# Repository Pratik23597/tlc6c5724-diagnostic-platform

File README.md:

# Portable Automotive RGB Lighting Diagnostic Platform

**Development and Validation of a Portable Automotive RGB Lighting Diagnostic Platform Using the TLC6C5724-Q1 Automotive LED Driver with Local Control and MQTT-Based Remote Monitoring through Node-RED**

University project, OTH Regensburg (2026) - Pratik Sukare

An ESP32-based test and control unit for the Texas Instruments **TLC6C5724-Q1**, a 24-channel constant-current RGB LED driver for automotive lighting. The platform drives all 24 outputs, runs the driver's built-in diagnostics, and reports faults both on a local TFT display and on a remote Node-RED dashboard over MQTT.

## Features

- **Driver interface:** SPI-based serial control of the TLC6C5724-Q1 with separate LATCH, GCLK/BLANK PWM timing and the ERR fault line
- **Diagnostics:** LED open/short (LOD/LSD), short-to-ground, adjacent-pin short (APS), IREF open/short, thermal warning and over-temperature, LOD/LSD self-test, NEG/GCLK integrity test, device status, raw SID readout, error clear
- **Validated under controlled fault conditions:** open and shorted LEDs, short-to-ground, adjacent-pin shorts and IREF faults are detected as expected
- **Non-blocking firmware:** no long delays in the main loop; MQTT commands are queued as pending commands and executed by the main loop; automatic LED tests run as a state machine
- **Six automatic LED tests:** RGB colour cycle, RGB phase rotation, sequential chase, brightness sweep, all white, all off
- **Local HMI:** 128x160 SPI colour TFT and three push buttons - works without any network
- **Remote monitoring:** Eclipse Mosquitto + Node-RED Dashboard 2 with a diagnostics page and a per-channel LED control page (grayscale, dot correction)
- **Network recovery:** retries saved Wi-Fi profiles, and returns to the preferred hotspot if the MQTT broker is unreachable

| Prototype | Node-RED diagnostics |
|---|---|
|  |  |

## Reports

- [Project report](reports/Project_Report.pdf) - design, implementation and results
- [Diagnostic validation report](reports/Diagnostic_Validation_Report.pdf) - test method, fault-injection steps and recorded results for every diagnostic

## Repository layout

| Path | Contents |
|---|---|
| `firmware/TLC6C5724_Diagnostic_Controller/` | ESP32 Arduino sketch, split by module (see below) |
| `node-red/flows.json` | Node-RED Dashboard 2 flow (import via *Menu > Import*) |
| `hardware/` | KiCad schematics (plus a PDF export) of the prototype, and the TLC breakout schematic and PCB layout |
| `mosquitto/` | Mosquitto demo config and a Windows launcher that starts Mosquitto and Node-RED and opens the dashboard |
| `docs/images/` | Architecture, prototype and dashboard figures |
| `reports/` | Project report (paper) and diagnostic validation report with test procedures and results |

Firmware modules:

- `TLC6C5724_Diagnostic_Controller.ino` - declarations and setup / main loop
- `TlcDriver.ino` - TLC frame building, serial transfer, GS/DC/BC configuration
- `Diagnostics.ino` - channel diagnostics, APS, IREF/device status, LOD/LSD, NEG/GCLK, SID debug
- `AutoTests.ino` - automatic RGB / phase / chase / brightness / static tests
- `NetworkMqtt.ino` - Wi-Fi profiles, MQTT commands, status publishing, recovery
- `DisplayUi.ino` - TFT pages and menu navigation
- `Buttons.ino` - push-button input
- `ProjectConfig.h` - MQTT topics, timing constants

## Build

1. Arduino IDE with the **ESP32** board package (board: ESP32 Dev Module).
2. Libraries: **PubSubClient**, **TFT_eSPI** (configure `User_Setup.h` for the 1.8" 128x160 SPI TFT used).
3. Copy `Secrets.example.h` to `Secrets.h` and enter your Wi-Fi and broker settings. `Secrets.h` is git-ignored.
4. On the laptop: install Mosquitto and Node-RED with `@flowfuse/node-red-dashboard`, import `node-red/flows.json`, then run `mosquitto/TLC6C5724_Demo_Start.bat` to start the broker and Node-RED and open the dashboard.

## References

- Texas Instruments, *TLC6C5724-Q1 Automotive 24-Channel, Full Diagnostics, Constant-Current RGB LED Driver*, datasheet
- Eclipse Mosquitto, Node-RED and Node-RED Dashboard 2.0 documentation

## License

MIT - see [LICENSE](LICENSE). Third-party code (e.g. ST HAL/CMSIS drivers, libraries) keeps its own license.

## Author

Pratik Sukare - [LinkedIn](https://www.linkedin.com/in/pratiksukare) | pratiksukare235@gmail.com

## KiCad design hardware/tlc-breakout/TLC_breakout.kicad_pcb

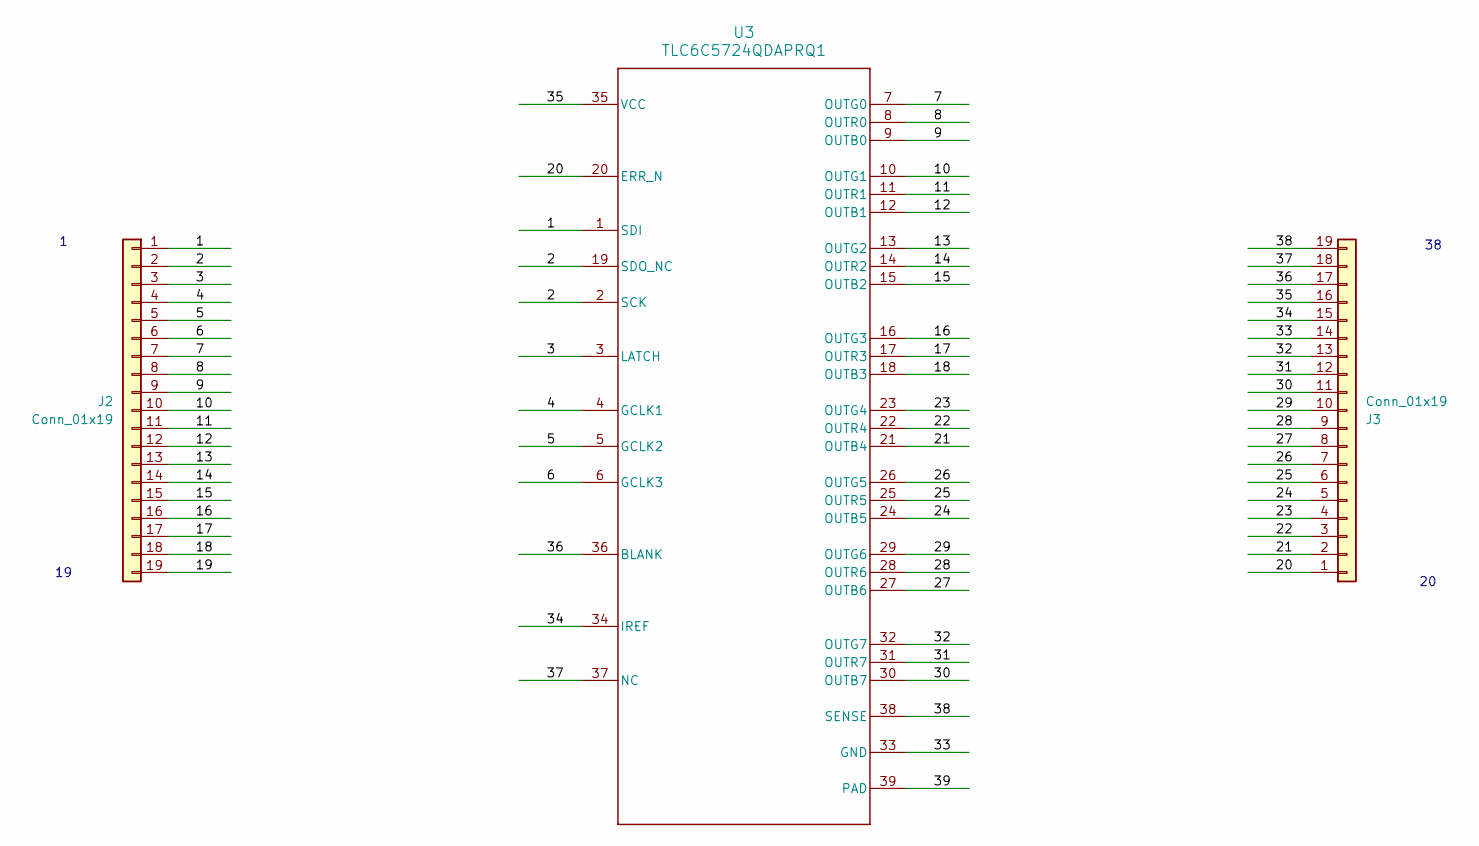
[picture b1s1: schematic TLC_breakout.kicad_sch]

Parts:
J2, J3: Conn_01x19; PinHeader_1x19_P2.54mm_Vertical
U3: TLC6C5724QDAPRQ1; DAP0038E

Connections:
/1: J2.1, U3.1 (SDI)
/2: J2.2, U3.2 (SCK), U3.19 (SDO_NC)
/3: J2.3, U3.3 (LATCH)
/4: J2.4, U3.4 (GCLK1)
/5: J2.5, U3.5 (GCLK2)
/6: J2.6, U3.6 (GCLK3)
/7: J2.7, U3.7 (OUTG0)
/8: J2.8, U3.8 (OUTR0)
/9: J2.9, U3.9 (OUTB0)
/10: J2.10, U3.10 (OUTG1)
/11: J2.11, U3.11 (OUTR1)
/12: J2.12, U3.12 (OUTB1)
/13: J2.13, U3.13 (OUTG2)
/14: J2.14, U3.14 (OUTR2)
/15: J2.15, U3.15 (OUTB2)
/16: J2.16, U3.16 (OUTG3)
/17: J2.17, U3.17 (OUTR3)
/18: J2.18, U3.18 (OUTB3)
/19: J2.19
/20: J3.1, U3.20 (ERR_N)
/21: J3.2, U3.21 (OUTB4)
/22: J3.3, U3.22 (OUTR4)
/23: J3.4, U3.23 (OUTG4)
/24: J3.5, U3.24 (OUTB5)
/25: J3.6, U3.25 (OUTR5)
/26: J3.7, U3.26 (OUTG5)
/27: J3.8, U3.27 (OUTB6)
/28: J3.9, U3.28 (OUTR6)
/29: J3.10, U3.29 (OUTG6)
/30: J3.11, U3.30 (OUTB7)
/31: J3.12, U3.31 (OUTR7)
/32: J3.13, U3.32 (OUTG7)
/33: J3.14, U3.33 (GND)
/34: J3.15, U3.34 (IREF)
/35: J3.16, U3.35 (VCC)
/36: J3.17, U3.36 (BLANK)
/37: J3.18, U3.37 (NC)
/38: J3.19, U3.38 (SENSE)
/39: U3.39 (PAD)

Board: 2 copper layers, 3 parts (0 on the bottom side), 37 nets, no tracks yet.
